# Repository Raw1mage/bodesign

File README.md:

# bodesign

_語言：**繁體中文** · [English](./README.en.md)_

**bodesign** 是一個 AI 電路設計（PCB）副駕，以**獨立的 MCP server** 形式交付。
它由對談與原始輸入檔驅動，走完整個 KiCad 設計生命週期——原理圖 → 佈局 → 製造——
產出可送廠的文件包，並以**展示**可靠度（對照已知良品的交叉檢核＋KiCad/SPICE/EMC）
而非「宣稱」可靠度。

它**與宿主無關、可獨立對外營運**：任何支援 MCP 的客戶端（IDE、agent，或你自己的 HTTP 呼叫端）
都能透過 MCP Streamable HTTP 驅動它，**不需要任何宿主外殼**。正式服務部署在 DockerLab CT105
（`http://192.168.100.141:8177/mcp/`，經 nginx ingress，`POST /invoke` 一律 403）；容器內部的
TCP port 從不直接對外 publish（BR_20260730d）。

## 它做什麼

- **匯入**整個專案資料夾（datasheet、原理圖、BOM、Gerber），唯讀。
- **規劃**需求：把自然語言規格轉成結構化計畫（並反問釐清），並把 C00 PRD 產出為**帶樣式的
  .docx**——重現真實 Rockbox C07-PRD Word 架構（封面＋改版紀錄表＋12 章＋章節內表格），範本以
  `.dotx` + JSON 架構描述預存在 server 端供重複使用。
- **生成** KiCad 符號與經 `kicad-cli` 驗證的原理圖（以參考設計為依據）。
- **佈局**（`pcbnew` 擺件＋DRC）並**匯出製造輸出**（gerber／鑽孔／pos／STEP）。
- **驗證**四層：ERC/DRC · 對照組交叉檢核 · SPICE · EMC/熱分析；其中對照組交叉檢核由
  **確定性參考比對器**（G7：純 Python Hungarian 配對＋Dice/屬性/連接性加權）執行，SPICE 以
  **datasheet 接地的 model 卡**（每筆參數帶 page-anchor 證據）取代泛用預設模型。
- **追蹤就緒度**，並為每個工程檔產出可讀伴隨檔（docx/pdf）與分享文件。所有「可靠度」皆以
  **可重現的確定性證據展示**（LLM 只負責上游抽取／裁決，驗證與比對全程不參與）。

## 近期變更

完整紀錄見 [`CHANGELOG.md`](CHANGELOG.md)。近期重點：

- **未發布（2026-10-23）** — **A2A 多 Agent 責任分層硬體設計治理體系（C03-C04）**：
  參考 `zhoushoujianwork/easyeda-agent` 治理機制，重構為嚴格 IDEF0 規範下的多 Agent 協作制度（規格：[`plans/workflow_guarded-hardware-governance/`](plans/workflow_guarded-hardware-governance/README.md)）。
  1. **微狀態機與零自我審批（Zero Self-Approval）**：實作 C03（`S0~S5`）與 C04（`P0~P7`）微狀態機，強制作者（EE/Layout）不可兼審查員；
  2. **密碼學憑證（Receipt）**：每次推進強制顯式列出 `not_checked` 未測軸向，P7 送廠前強制人類授權（天條 3）；
  3. **阻礙中樞（Blocker Hub）**：結構化異常派工（`BLK-nnn`）與重試邊界防止循環；
  4. **認證標準電路積木庫**：提供 `usb_c_sink`、`power_ldo_3v3`、`power_dcdc_buck`（含 $C_{FF}$）、`esd_protection_array`，自動處理引腳與佈局約束；
  5. **確定性佈局整潔原語**：吸附網格（`grid_snap`）、線性元件對齊（`distribute_passives`）、焊盤絲印避讓（`silk_tidy`）；
  6. **視覺化 DRC 局部裁切**：自動生成 5mm×5mm 高對比度裁切（100px/mm PNG / SVG），為多模態 Review 提供物理真相；
  7. **Landing Verbs 整合**：新增 `c03_substate_advance`、`c04_substate_advance`、`circuit_block_apply`、`layout_tidy`、`blocker_record` 5 組宿主原生動詞。
- **未發布（2026-07-06）** — **BR_20260706 五筆 BR 閉環（schematic 交付保真閘群）**：spec
  `eda_schematic-draftsman-quality` extend DD-8..DD-11 至 living——`compose_schematic`
  新增 `fidelity`（net 劃分保真閘，抓 ERC 盲區的共線熔合短路）與 `density_budget`
  （頁面密度超標 fail-fast 強制分頁）；kicad_emit 防熔合 guard（確定性 jog 錯開）；
  `qa_svg_text` 渲染層文字 QA landing verb；`/tmp/engpatch` 部署漂移源退場 +
  `engine_rev` 回報；SKILL.md 交付契約六硬規。62 tests OK。
- **未發布（2026-07-05）** — **skill 語料去誤導化**：稽核出 18 筆會誤導 agent 的語料
  （含 R20 HV 間距跨欄拼湊安全 bug，裸外層板低壓間距偏小 4.6 倍）全數修畢；
  建立 provenance 三級制（`[primary:]`/`[fab:]`/`[rot]`，經驗值禁入 DRC gate）與
  clean-result 邊界語紀律。雙盲 eval：新版 6/6 vs 舊版 0/6。
- **未發布（2026-07-04）** — **跨 spec extend：copper-clearance checker 落地**：畢業
  `design-ir/net-role-extension`（封閉 NET_ROLES enum）與 `gerber-core/copper-geometry-parser`
  （真實 edge-to-edge 銅箔幾何）兩 spec，新增 `copper_clearance.py` 消費之，把
  `control.dfm.ipc-clearance-voltage` 由 T-B stub 翻為 T-A landed（landed 8→9）。
  拒絕 false-green——landed 由 9 個測試（含 6 個 no-fabrication fail-fast 守衛）背書。
- **未發布（2026-07-03）** — **C04 誠實機制接線**：修復 aiguard 踩坑的工具層根因。新增
  C04 上游履約 gate（C03 未落 netlist → `blocked_upstream_c03_missing`，不再誤報 drafted），
  把去孤兒化的 `classify_product_feasibility`（tier 分診，無 signals 不臆測）與
  `emit_si_constraint_export`（Tier-3 SI 交手）接進 C04 emit/readiness；41 tests 綠。
- **0.2.1（2026-07-03）** — 第 5 道信任層 **PRD↔BOM 履約 crosscheck gate**（C04 缺口治理）：
  驗收發現 C00 PRD 定義的晶片模組未落到板上，以「一級一級治」補 L1 履約 gate
  （`bodesign_prd_bom_crosscheck`）、L2 Vault-Absent 降級協議、L3 NPN linear sink 重設計；
  C04 全鏈實跑 `gate=PASS` + DRC clean。另落地 atopile DSL 前端（工具 43→45）。
- **0.2.0（2026-07-02）** — R13 compute/landing split（52 verbs 落地）+ WebDAV working cache。

## 架構圖

### A2A 多 Agent 硬體治理工作流架構（C03-C04 責任分層與微狀態）

完整規格與生命週期設計見 [`plans/workflow_guarded-hardware-governance/`](plans/workflow_guarded-hardware-governance/README.md)。

**A2A 治理體系 IDEF0 功能分解（A0）**

**A2A 治理體系 GRAFCET 執行流程（S0~S5 ➔ P0~P7 & Blocker 派工修復迴圈）**

### 系統全域產品架構（PCB AI Viewer）

完整規格見 [`specs/product/pcb_ai_viewer/`](specs/product/pcb_ai_viewer/README.md)。

**IDEF0 功能分解（A0）**

**GRAFCET 執行流程（生成迴圈）**

## 執行

**Docker（可攜，建議）** — 內含 KiCad 9（`kicad-cli` + `pcbnew`）＋ LibreOffice ＋整套工具鏈：

```bash
./mcpctl.sh start     # 建置映像＋啟動容器（UDS 於 ./.run/bodesign.sock）
./mcpctl.sh status    # 健康檢查＋socket
./mcpctl.sh log       # 追蹤日誌
./mcpctl.sh stop
```

**主機（不用 Docker）** — 需要 PATH 上有 `kicad-cli`、`pcbnew`、`soffice`、`ngspice`：

```bash
pip install -r services/mcp/requirements.txt
python services/mcp/server.py --transport http --uds .run/bodesign.sock --port 8077
# 或 --transport stdio 供 IDE/agent 直接使用
```

## 連線（MCP）

MCP **Streamable HTTP**：

- **正式（DockerLab CT105，預設）**：`http://192.168.100.141:8177/mcp/`——僅限 LAN，nginx ingress
  封鎖 `POST /invoke`（403），只開放 `/healthz`、`/mcp`、`/files`。部署清單與發布 SOP 見
  [`deploy/dockerlab/`](deploy/dockerlab/README.md)。
- **本機開發**：`BODESIGN_DEV=1 ./mcpctl.sh start` 後經 UDS `unix:///…/.run/bodesign.sock:/mcp/`。
  兩者擇一，不要同時跑。
- 容器內部 TCP `:8077` 從不直接 publish（BR_20260730d：publish 會把未認證的 `POST /invoke`
  暴露在所有介面上），對外一律經 ingress。

註冊資訊見 [`mcp.json`](mcp.json)。開啟服務的 `/` 即是即時的自我說明指南——
安裝、檔案模型、電路設計工作流，以及 `/tools`、`/tools/{name}` 的完整 tool-call schema。

## 檔案模型（兩平面，0.2.0）

**Landing plane（本地直跑，零 token 往返）** — 52 個確定性、只碰專案目錄的 verb
（C00–C06 scaffold/readiness/emitters、orchestration spine、純函數）**不再是 MCP 工具**，
改由 agent 在主機以自己的身分直接執行：

```bash
python3 skills/bodesign/scripts/gate.py --list        # 權威 verb 清單
python3 skills/bodesign/scripts/gate.py <verb> --repo <abs專案路徑> [--json '{…}' | --arg k=v]
```

誤把已落地的名字當 MCP 工具呼叫，會收到 typed error `TOOL_LANDED`，內附等效的 gate.py 指令。

**Compute plane（容器 token 檔案模型，docxmcp 風格）** — 重工具鏈（pcbnew/kicad-cli/ngspice/
渲染/3D）留在容器內的 43 個 MCP 工具。bodesign **不內含任何工作資料**：檔案只走一條路——WebDAV
工作區。Agent 呼叫 opencode runtime verb `system-manager_webdav_mount(app="bodesign")` 取得
`mount_path` + `token`；把輸入檔放進 `mount_path`，將 token 傳給任一工具（路徑參數在工作區樹內解析），
產出檔直接在 `mount_path` 讀回。伺服端工作資料依 TTL 自動垃圾回收；容器看不到主機路徑。

**Working cache（WebDAV，消滅整包進出儀式）** — 需要多檔往返的交付物改用伺服端工作快取：
`bodesign_cache_provision`（由 opencode runtime 呼叫，不由 agent 呼叫）回傳 token + 絕對
`mount_url`（`…/dav/{token}/`）+ 選用的專屬 Basic 憑證；重工具直接寫入快取命名空間，產出檔在掛載目錄
直接可見——不需匯出步驟。`bodesign_cache_close` 回收工作區。每個 cache 依擁有者隔離，
免於 idle 回收（長 safety-net TTL 把關）。

## Skill 配對

bodesign（MCP）是**生成的那一半**；配套的 **`bodesign` skill** 是工作流大腦（C00–C07 生命週期、
誠實契約、各階段 SOP），**並且**承載分析／文件引擎——`kicad`（原理圖／PCB／Gerber 分析）與
`kidoc`（工程文件）現在以 `engines/kicad`、`engines/kidoc` 的形式住在那裡，所以請安裝 `bodesign`
skill，而非獨立的 `kicad`／`kidoc`。分工是雙向的：skill 驅動本 MCP 的 `bodesign_*` 工具來**生成**，
而 MCP 的驗證工具（`bodesign_simulate`／`analyze_emc`／`analyze_thermal`）回頭呼叫 skill 的引擎來
**分析**（透過 `BODESIGN_KICAD_SKILL` 解析，預設 `~/.claude/skills/bodesign/engines/kicad`）。

其餘成熟的模擬／採購／製造 EDA skill（`spice`、`emc`、`datasheets`、`bom`、distributors、fab），
連同獨立的 `kicad`／`kidoc`（legacy，已併入 `bodesign` skill），都可從執行中的服務在 `/skills/`
下載（整包＋個別 skill），安裝到你的 skill 目錄。

skill 在執行層之上再加一層**設計判斷**（各階段的 reference：C01 reduction-lens＋Ashby 選材、
C02 DFM/DFA/IP 密封＋幾何作圖迴圈、C03 EE advisory＋「腳位→電路」合成法、C04 stackup/HDI/SI）。
跨站不收斂（面積／散熱／高度 budget、C06 verdict fail）會以既有 `BlockerReturn` **回饋**到負責的
階段並擋住下游完成（遞迴自我修正）。一開始就用**可行性 triage** 從 C00 估算分級(Tier 1 可直接
投板／2 需人類 SI 簽核／3 HDI 級交專業 EDA)，讓「給 C00，得 C01–C04」對每個產品**誠實**；
Tier-3 由 `emit_si_constraint_export` 產出中性 SI 約束包（JSON＋CSV＋逐工具對應），把繞線硬牆變成
乾淨交接而非斷點。

## 目錄結構

```text
bodesign/
├── services/mcp/                 MCP server —— 產品的唯一對外介面
│   ├── server.py                 工具分派、token 路徑解析、UDS+TCP 雙綁定、自我說明網頁
│   ├── token_store.py            docxmcp 式 token 檔案儲存 ＋ TTL/GC
│   ├── requirements.txt
│   └── assets/skills/            EDA skill 套件（13 個 tarball ＋整包 bundle ＋ MANIFEST.md）
├── packages/                     通用能力函式庫（無產品專屬碼）
│   ├── shared/                   共用契約 ＋ data_root()（程式↔工作資料隔離邊界）
│   ├── design-ir/                DesignIntent 等中介表示（IR）；compare/ 子模組＝確定性
│   │                             參考比對器（G7：純 Python Hungarian＋Dice/屬性/連接性加權＋FlexiblePin）
│   ├── component-kb/             可重用零件知識（datasheet 萃取）；spice_card.py＝datasheet 接地
│   │                             SPICE model 卡（vault L4 → cascade tier-1，確定性、byte-identical）
│   ├── doc-core/                 pin-table／文件產生工具
│   ├── source-core/              來源／證據契約
│   ├── reverse-core/             專案匯入、伴隨檔渲染、文件輸出、board 重建
│   ├── gerber-core/              Gerber／鑽孔解析 ＋ 預覽
│   ├── eda-bridge/               KiCad 橋接：符號／原理圖／佈局／製造／BOM／SPICE／EMC；
│   │                             simulate 標注 model_source（vault-grounded｜generic-default）
│   ├── workflow-core/            需求規劃、證據蒐集、就緒度羅盤、對照組交叉檢核、
│   │                             可行性 triage（C04 交付分級）、跨站對帳閘、SI 約束交接；
│   │                             驗證紀律 G1–G7（需求契約／設計審查閘／crosscheck＋root-cause／
│   │                             ValidationEvidence 回流／workflow plan 衍生）
│   ├── storage-core/             客戶自有專案登錄
│   └── kicad-plugin/             in-KiCad Action Plugin 契約（roadmap）
├── specs/                        規格／知識庫（plan-builder）
│   ├── architecture.md           跨領域架構索引
│   ├── product/pcb_ai_viewer/    已上線（living）產品設計規格 ＋ IDEF0/GRAFCET SVG ＋ 中文 README
│   ├── feature/eda-mcp-toolchain/  已上線（living）C04 EDA 工具鏈規格（routing/finishing MCP 工具）
│   ├── workflow/verification-discipline/  已上線（living）參考優先驗證紀律規格（G1–G7）
│   └── knowledge/datasheet-spice-models/  已上線（living）datasheet 接地 SPICE model 卡規格
├── tests/                        測試（乾淨 clone 全綠；資料相依測試自動跳過）
├── Dockerfile · docker-compose.yml · mcpctl.sh   容器封裝 ＋ 操作
├── mcp.json                      MCP 註冊資訊
└── README.md · README.en.md      本文件（繁中／英）
```

> bodesign **不內含任何工作資料**；客戶專案樹只在執行期經 token 儲存進入，或由外部 `data_root()`（`BODESIGN_DATA_DIR`）讀取。

## 可靠度邊界

交叉檢核＋SPICE/EMC 是**矽前風險層**——在打樣前抓出問題。它們**不取代**實驗室／工廠的
認證 EMC／EVT／DVT；且 bodesign 在未經確定性驗證＋明確批准前，不會輸出任何送廠檔案。

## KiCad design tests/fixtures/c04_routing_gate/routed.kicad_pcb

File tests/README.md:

# tests

Fixture-driven tests for MCP tools, FastAPI endpoints, component knowledge extraction, reconstruction interfaces, Gerber validation, and the `/bodesign/` viewer.

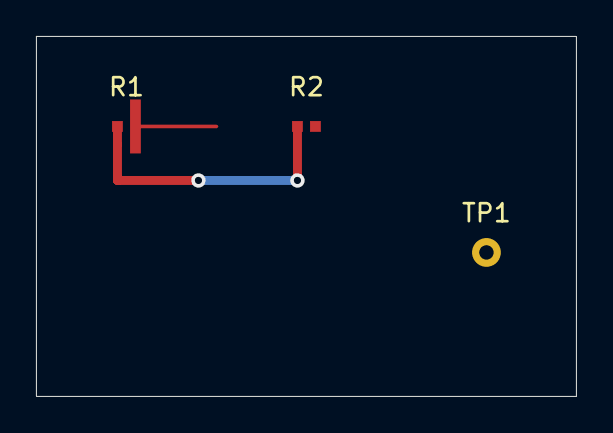
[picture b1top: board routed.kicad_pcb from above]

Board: 2 copper layers, 30.0 x 20.0 mm, 3 parts (0 on the bottom side), 2 nets.

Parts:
R1, R2: R_0402_1005Metric
TP1: TP_1.6

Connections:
GND: R2.2, TP1.1
PWR: R1.1, R2.1

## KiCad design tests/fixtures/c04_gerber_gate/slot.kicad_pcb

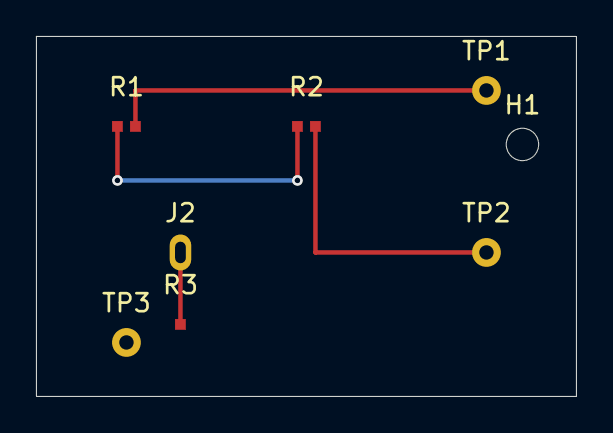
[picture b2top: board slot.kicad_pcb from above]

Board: 2 copper layers, 30.0 x 20.0 mm, 8 parts (0 on the bottom side), 4 nets.

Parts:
H1: MountingHole_1.8mm
J2: SLOT_TEST
R1, R2, R3: R_0402_1005Metric
TP1, TP2, TP3: TP_1.6

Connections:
GND: R2.2, TP2.1
N1: R1.1, R2.1
N2: R1.2, TP1.1
SLOTN: J2.1, R3.1

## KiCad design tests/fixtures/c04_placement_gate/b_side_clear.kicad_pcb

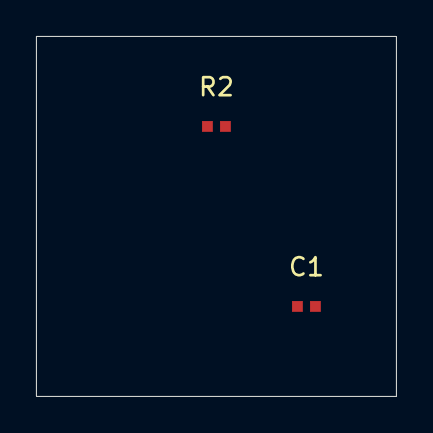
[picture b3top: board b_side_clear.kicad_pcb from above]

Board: 2 copper layers, 20.0 x 20.0 mm, 3 parts (1 on the bottom side), 3 nets, no tracks yet.

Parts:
C1: C_0402_1005Metric
R1, R2: R_0402_1005Metric

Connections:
GND: C1.2, R2.2
N1: C1.1, R1.1
N2: R1.2, R2.1
